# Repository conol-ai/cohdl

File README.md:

# CoHDL

CoHDL is the programming language that makes schematic (PCB) design AI-native — the way software became AI-native. AI generates and repairs hardware; the compiler is the oracle that grades it.

This is the **v2 ground-up implementation**, restarted 2026-07-13 from the redesigned language specification. The central thesis of the redesign: **strictness buys expressiveness** — push correctness into the type system wherever a mistake is structural (wrong units, unresolved pins, unsatisfied trait bounds), and reserve DRC only for genuinely emergent, whole-graph checks (net voltage, driver conflicts).

The previous implementation lives on the [`legacy`](https://github.com/conol-ai/cohdl/tree/legacy) branch. It is not being fixed; this is a fresh build informed by its lessons.

## Design repository

The source of truth for the language design is the Coherent Design Repository on conol.ai:
<https://conol.ai/share/note/tqrnb5h4l0dv8c14dkd17h4l>

A snapshot (taken 2026-07-13) is committed under [`docs/design/`](docs/design/). Key documents:

- [MVP Definition](docs/design/09-mvp-definition.md) — the scope line, demo scenario, and exit criteria this repository was built toward
- [Language Specification](docs/design/10-language-specification.md) — the compiled statement of what the language is (Accepted RFCs only)
- RFC-001…RFC-007 — the seven Accepted P0 RFCs: units-as-types, pin connection-obligation typing, trait satisfaction at impl time, DRC/type-system reclassification, collision-free designator allocation, nested fn call semantics, generics-over-specs
- RFC-008…RFC-018 — the post-MVP Accepted RFCs (compiler-implemented, with named open gaps recorded in [`docs/compliance-report.md`](docs/compliance-report.md) — notably RFC-016/017 on-disk dependency loading is not yet built, and RFC-014/015 real-client/partner acceptance passes remain open): structural variants, `cohdl fmt`, `cohdl check --json`, the formal error-code registry, `#[intent]` annotations, layout constraints, the LSP server (`cohdl lsp`, [`docs/lsp.md`](docs/lsp.md)), the IPC-2581 handoff document (`build --emit ipc2581`, [`docs/ipc2581.md`](docs/ipc2581.md)), the module system, the library registry, the pad/footprint format (`pad`/`footprint` geometry → `.kicad_mod` + IPC-2581 pins), and a real VS Code extension (`editors/vscode/`, packaging `cohdl lsp` with a TextMate grammar — RFC-019)

## MVP (v0.1) scope

The smallest slice of the spec that proves the thesis end-to-end:

1. **Parser** — traits, devices, free-standing `impl`, `fn` declarations/calls (nested), design bodies (`inst`, `net`, `nc`), the eleven unit-type literal forms
2. **Type checker** (the heart) — zero-coercion unit types, pin connection-obligation exhaustiveness, trait satisfaction with explicit mapping, generic resolution with trait-bound checking, nested fn expansion with cycle detection
3. **Residual DRC** — exactly four rules: voltage-exceed, polarity-mismatch, single-driver, multi-driver
4. **Designators** — collision-free allocator, `design.lock` with tombstones, `#[designator("…")]` overrides
5. **Codegen** — KiCad `.net` netlist + BOM CSV
6. **Minimal std library** — only the universal traits every component package needs
7. **Repair harness** — generate → check → repair loop driving an LLM against the compiler's diagnostics

The proof: an AI writes a board from a plain-language spec, the type checker catches its structural mistakes as precise compile errors, the AI repairs them from those diagnostics, and the result is a real, importable KiCad netlist with an honest BOM.

## Status

All MVP exit criteria are met, and all nineteen Accepted RFC areas (RFC-001…019) have implementation work with conformance suites. That is deliberately not a claim of full accepted-text compliance: requirements that are incomplete (e.g. RFC-014's real-editor acceptance pass and RFC-015's real-partner/Quilter import pass — both open), deliberately deviating (e.g. the E9xx code assignment, D003's role-aware reading, RFC-015's constraint mapping riding vendor extensions rather than native IPC semantics), or unrepresentable pending note-side amendments (e.g. RFC-013's E1005) are each recorded with rationale in the ledger, [`docs/compliance-report.md`](docs/compliance-report.md). Tested (`cargo test` — [`tests/exit_criteria.rs`](tests/exit_criteria.rs) maps 1:1 to the MVP checklist; each post-MVP RFC has its own conformance suite under `tests/`). The demo loop has run end-to-end: see [`docs/demo/`](docs/demo/) for transcripts (including a genuine E701 unresolved-required-pin catch + repair) and the emitted netlist/BOM. RFC/decision-record accuracy was audited claim-by-claim: [`docs/compliance-report.md`](docs/compliance-report.md). The KiCad checkpoint has been executed with real KiCad (pcbnew imported the netlist, resolved all footprints and pads; board + render in `docs/demo/`).

## Install

One line (macOS and Linux; installs to `~/.cohdl/bin`):

```sh
curl -fsSL https://raw.githubusercontent.com/conol-ai/cohdl/main/install.sh | sh
```

Prebuilt binaries (and their `sha256sums.txt`) are attached to every
[`vX.Y.Z` release](https://github.com/conol-ai/cohdl/releases); Windows users
download `cohdl-vX.Y.Z-x86_64-pc-windows-msvc.tar.gz` by hand. An installed
binary updates itself with `cohdl self-update` (`--check` reports without
installing). Building from source stays `cargo build` (toolchain pinned by
`rust-toolchain.toml`).

## Using it

```sh
cargo run -- check examples/sf32-miniboard       # SF32 miniboard: SiFli BLE eval board
cargo run -- build examples/rpi-pico2            # + designators, parts, KiCad .net + BOM CSV
cargo run -- check examples/rpi-pico2 --json     # structured diagnostics (RFC-010)
cargo run -- build examples/rpi-pico2 --emit ipc2581  # + IPC-2581 handoff document (RFC-015)
cargo run -- build examples/rpi-pico2 --emit kicad_pcb # + a native KiCad 10 board file — no KiCad needed
cargo run -- build examples/rpi-pico2 --emit easyeda   # + an EasyEDA / LCEDA Pro netlist (.enet)
cargo run -- build examples/rpi-pico2 --supplier acme   # + supplier BOM/map/CPL (RFC-034)
cargo run -- fmt lib --check                     # canonical-form gate (RFC-009)
cargo run -- lsp                                 # LSP server on stdio (RFC-014, docs/lsp.md)
cargo run -- search TPS59650                     # search registry packages + public parts
cargo run -- search TPS59650 --json              # the same bounded results as JSON
python3 harness/repair_loop.py                   # the generate → check → repair demo
```

Physical builds of placed designs also write `out/<name>-cpl.csv`, the
supplier-neutral five-column placement CSV. Under RFC-034,
repeatable `--supplier ID` selects each instance's own primary or eligible
alternate binding and writes `out/<name>-<ID>-bom.csv`,
`out/<name>-<ID>-map.json`, and (for physical builds)
`out/<name>-<ID>-cpl.csv`. The map preserves the selected entry identity and
placement transform; `tools/smt_pos.py --map` can apply it to the emitted
KiCad board. `--logical-only` remains a logical-artifact boundary: it emits
no neutral or supplier CPL, even when `--supplier` is present. Supplier BOM
and map remain available in that mode. Repeatable build option
`--bottom-rotation ID=VALUE` selects the bottom-side angle convention (`kicad`
or `mirrored`) for a supplier CPL; IDs must also be selected by `--supplier`
and default to `kicad`. Schema-2 maps record the convention actually used,
including in logical-only builds, and `tools/smt_pos.py --map` applies the same
rule (schema-1 maps retain `kicad` compatibility).

`cohdl search QUERY [--json]` is read-only discovery: it needs no project and
no registry login. Queries are trimmed, must contain at least three Unicode
scalar values, may be at most 128 UTF-8 bytes, and may not contain control
characters. Results identify the owning package and exact most-recently-
published version as well as importable public part paths and matching primary
or alternate manufacturer/MPN data; a valid query with no matches still exits
successfully. Use the standard option terminator when a literal query starts
with a hyphen, for example `cohdl search -- -12V`. “Most recently published”
is publication chronology, not the greatest semantic version chosen by an
unversioned `cohdl add`/`cohdl update`.
The package and part result families are bounded independently; each exposes
`has_more` when truncated and never a total count. Human output separates the
two families, while `--json` returns the same rows as one discovery document.
For rollout, owners of existing packages backfill the current searchable
version once with `cohdl docs --publish`; this does not change its tar or hash.

`std` is a core-traits-only prelude; it carries no devices, parts, pads, or
footprints. Shipped component packages include `passive`, `connectors`, `usb`,
`esd`, `diode`, `flash`, `ldo`, `led`, `mic`, `mosfet`, `osc`, and
manufacturer packages for Espressif, Raspberry Pi, Richtek, ST, and TI.
Projects pin every package they use to an exact version under
`[dependencies]`; see [`lib/README.md`](lib/README.md) for the complete
namespace map.

Two reference designs live in `examples/`: Raspberry Pi **Pico 2** and the
**SF32 miniboard**. (The **OpenMicro** macropad — the wired STM32F072 v1 and
its wireless SF32LB52 successor v2 — graduated to its own repository,
`openmicrokbd`, which carries the whole product: hardware source, firmware,
host app, and fab releases under `hw/v1/` and `hw/v2/`.)

An **AI voice robot-dog mainboard** is in progress and not yet in the tree; its
exit-criteria test is checked in but ignored until the example lands. It
combines an ESP32-S3-N8R2, stereo I2S microphones,
isolated speaker playback, a translated 1.8 V IMU domain, USB-C, a protected
default-off 7 A actuator rail, and eight 5 V servo PWM channels. Keyed 4/6-pin
Micro-Fit harnesses prevent the BEC input from being interchanged with a leg.

### Build artifacts

`cohdl build` writes to `out/` (or `--out-dir`): the KiCad netlist (`<name>.net`), the BOM (`<name>-bom.csv`), the designator lock (`design.lock` in the project root), a `.kicad_mod` per pad-bearing footprint under `out/footprints/` (RFC-018), and — only when the design declares layout metadata — the layout-constraint artifact `<name>-layout.json` (schema: [`docs/layout-json.md`](docs/layout-json.md)). With `--emit ipc2581` it additionally writes the IPC-2581B1 handoff document `<name>.xml` (RFC-015; [`docs/ipc2581.md`](docs/ipc2581.md)), with `--emit kicad_pcb` a native KiCad 10 board file `<name>.kicad_pcb` — placements, net-bound footprints, and the board outline, with no KiCad installation involved ([`docs/kicad_pcb.md`](docs/kicad_pcb.md)), and with `--emit easyeda` an EasyEDA / LCEDA Pro netlist `<name>.enet` for **File → Import → Netlist** ([`docs/easyeda.md`](docs/easyeda.md)); the flags compose. Stale layout/IPC/board artifacts are removed when their source data is gone (the IPC document only if CoHDL wrote it — its completeness marker establishes ownership).

### Looking at a design

A checked design can be read back as an interactive schematic-style board —
every instance, net and pin the compiler resolved, searchable and traceable,
with datasheets and to-scale footprint previews in a side panel. It is a
read-only projection: the `.cohdl` source stays the only thing that defines
the circuit.

On macOS, download the signed, notarized app from the latest
[`explorer-v*` release](https://github.com/conol-ai/cohdl/releases?q=explorer&expanded=true)
(mount the DMG, drag to Applications, pick a project). Or run it from source:

```sh
cd explorer/web && npm install && npm run build   # once
cd ../extractor
COHDL_LIB=../../lib cargo run --release -- ../../examples/rpi-pico2 \
    --serve --dist ../web/dist --port 5199        # http://127.0.0.1:5199/
```

Editing any source file re-extracts and refreshes the page within ~500 ms; a
source that fails to compile keeps the last good view and shows the
diagnostics. Extraction, layout and wire routing are deterministic code — the
same source always draws the same board. An agent's only input is the
partition file `explorer/views/<Design>.view.json`, which names the page tabs
and the region each part belongs to; the contract for writing one is
[`explorer/skills/view-gen/SKILL.md`](explorer/skills/view-gen/SKILL.md).
See [`explorer/README.md`](explorer/README.md).

### Exit codes

`0` = clean (warnings and a valid no-match search are allowed); `1` = the
accepted command failed (source errors, non-canonical `fmt --check`, or an E1204
search registry/protocol failure); `2` = invocation-level failure (bad flags,
an invalid search query, missing project, design selection, nothing to build);
`3` = `cohdl suppliers` found an `unknown` or `mismatched` audited binding
(out-of-stock, unbound, and unlisted suppliers do not change the exit code).
Human diagnostics use stderr. A successful `search --json` emits its discovery
document on stdout, and an E1204 failure in that mode emits the existing
diagnostic JSON there; bad invocations remain prose-only on stderr. See the
formal [`docs/error-codes.md`](docs/error-codes.md) registry. Note: RFC-010's
text reserves stderr prose for pre-collection failures, so classifying
post-collection selection failures this way is a documented deviation pending
a note-side amendment (or a v2 schema envelope).

## License

MIT — see [`LICENSE`](LICENSE). This covers the compiler crate, the libraries
under `lib/`, the reference designs in `examples/`, the registry
server in `registry/`, the VS Code extension in `editors/vscode/`, and the
tooling in `tools/` and `harness/`.

Third-party material is not covered by that grant: the manufacturer documents
under `lib/*/docs/` keep their owners' terms, KiCad-derived footprints are
CC-BY-SA-4.0 as each such package records in its manifest and license files, and the supplier
catalog facts and assembly-preview captures under `tools/sourcing_data/` are
described in [`tools/sourcing_data/NOTICE.md`](tools/sourcing_data/NOTICE.md).

Every package published to registry.cohdl.org must declare its own
`[package] license`; every package shipped under `lib/` declares `MIT`.

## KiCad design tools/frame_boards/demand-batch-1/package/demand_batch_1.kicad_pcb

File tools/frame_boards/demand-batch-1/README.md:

# Demand batch 1 preview board

**Built, not previewed, not evidence.** This directory holds the input
manifest for an assembler preview of ten part numbers whose library parts
are unbound. Nothing here is a binding, and no frame row is written from
it.

## Why it exists

The parts added on 2026-11-25 (`load-switch` 0.2.2, `diode` 0.1.3,
`transistor` 0.2.2) have candidate LCSC part numbers but no
`supplier lcsc` clause: a binding needs a frame row with evidence in
`tools/sourcing_data/jlc_frames.json`, and that evidence is an assembler
preview read by a person. This board is the input for that preview.

## Rows

Each row declares a local part with the candidate part number on the
library device and land, with a zero mapping, placed four times: top 0 and
37 degrees, bottom 0 and 37 degrees, in 14 mm boxes on a 16 mm pitch (the
preview board 5 layout).

| Library part (unbound) | Candidate | Land |
|---|---|---|
| `load_switch::LOADSW_TPS2553DBVR` | C55266 | `load_switch::FP_TI_DBV0006A` |
| `load_switch::LOADSW_TPS2553DBVR_1` | C111738 | `load_switch::FP_TI_DBV0006A` |
| `load_switch::LOADSW_TPS2552DBVR` | C46506 | `load_switch::FP_TI_DBV0006A` |
| `diode::TVS_VISHAY_SMBJ30A` | C1973126 | `do214::DIOM5336X265N` |
| `diode::TVS_MDD_SMBJ30A` | C113998 | `do214::DIOM5336X265N` |
| `diode::TVS_HONGJIACHENG_SMBJ30A` | C19077584 | `do214::DIOM5336X265N` |
| `diode::TVS_VISHAY_SMBJ30CA` | C553967 | `do214::DIOM5336X265N` |
| `diode::TVS_MDD_SMBJ30CA` | C113999 | `do214::DIOM5336X265N` |
| `diode::TVS_HONGJIACHENG_SMBJ30CA` | C19077585 | `do214::DIOM5336X265N` |
| `transistor::FET_BSS138` | C52895 | `sot::SOT3P190X290X130N` |

The manufacturer, MPN, package, class and stock in each row are what the
part's JLCPCB page read on 2026-11-25. None of the ten is in
`tools/sourcing_data/lcsc_map.json`.

## State on 2026-11-25

- `manifest.json` was written by hand in the input format of
  `tools/jlc_frame_board.py`; there is no generator script for it.
- **The board package is built** (library at commit `537c43d`, Python
  3.11.0rc1, `kicad-cli` 10.0.8):

  ```sh
  python3.11 -I tools/jlc_frame_board.py tools/frame_boards/demand-batch-1/manifest.json \
    -o BOARD --cohdl target/debug/cohdl
  ```

  It reported `generated 40 placements`. A 180 x 75 mm board.
- `package/` is a copy of that output: `fabrication/` (Gerbers, drill file
  and `SHA256SUMS`), `demand_batch_1.kicad_pcb`,
  `demand_batch_1-lcsc-bom.csv`, `demand_batch_1-lcsc-cpl.csv`,
  `demand_batch_1-cpl.csv` and the tool's `CHECKLIST.md`.
- `render/` holds `kicad-cli pcb render` images of that board file:
  `top.png` and `bottom.png` (each side seen from its own side), and one
  480 px crop per copy, named `<C-number>_<designator>_<side>_<angle>.png`
  (16 mm square about the placement). The renders show our copper and
  silkscreen only. They contain no supplier model and are not a preview.
- **Checked against the board file, not against any preview:** all ten part
  numbers are in the LCSC BOM with four designators each; every part
  number has a top 0, top 37, bottom 0 and bottom 37 copy at its manifest
  position; each copy is on the intended land with the intended pad
  numbers and sizes (six 1.1 x 0.6 mm pads on `FP_TI_DBV0006A`, two
  2.10 x 2.26 mm on `DIOM5336X265N`, three 0.8 x 0.9 mm on
  `SOT3P190X290X130N`).
- **The silkscreen carries reference designators.** Preview board 5 left
  them out of the Gerber silkscreen because text beside a part disturbed
  the measuring script's readings. Regenerate without them if the readings
  are to be measured by `measure_preview.py`.
- Nothing was uploaded. No preview was run, no reading exists, and no row
  of `tools/sourcing_data/jlc_frames.json` or `lcsc_map.json` was written.

## What a person still has to confirm

For each part number, on JLCPCB's assembly preview of the built board:

1. The model is drawn, on our pads, on all four copies.
2. Pin 1 (SOT-23-6, SOT-23) or the cathode band (unidirectional SMBJ) sits
   at our pad 1; if it reads a quarter or half turn, that reading is a
   candidate rotation, to be confirmed on a second board with the
   candidate applied, as preview board 5 did.
3. For the bidirectional SMBJ parts, the body's long axis lies along the
   pad axis and is centred (the body-only rule of
   `docs/library-supplier-plan.md`); orientation is known mod 180 only.

Only after that review does a part get a frame row with `evidence`, a map
row from a promoted `tools/lcsc_backfill.py` run, and its
`supplier lcsc` clause in a new package version.

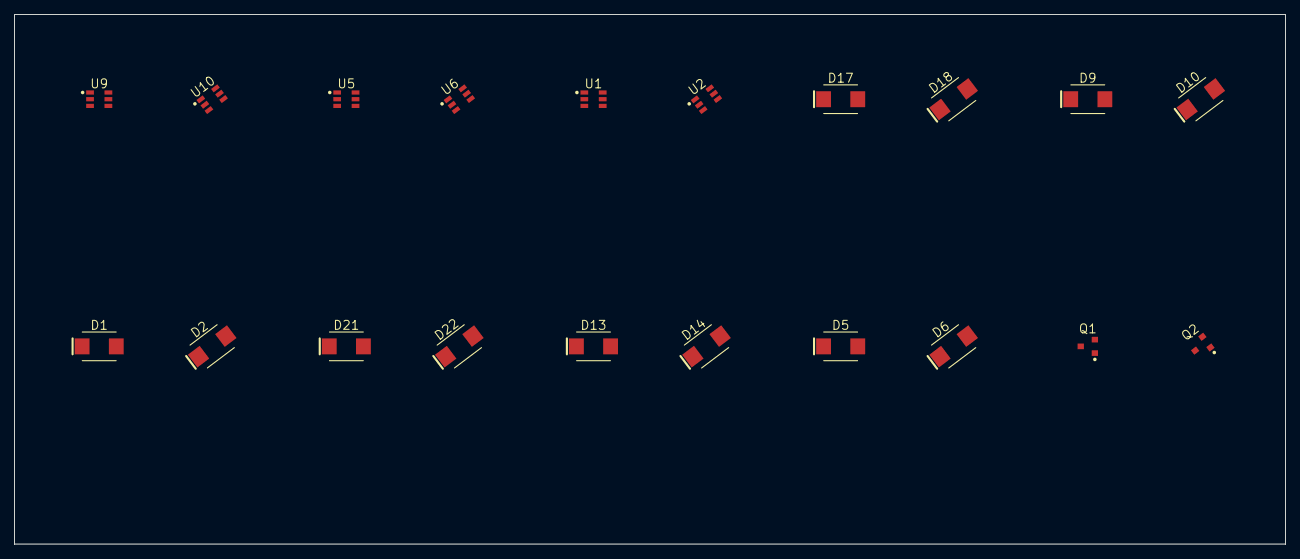
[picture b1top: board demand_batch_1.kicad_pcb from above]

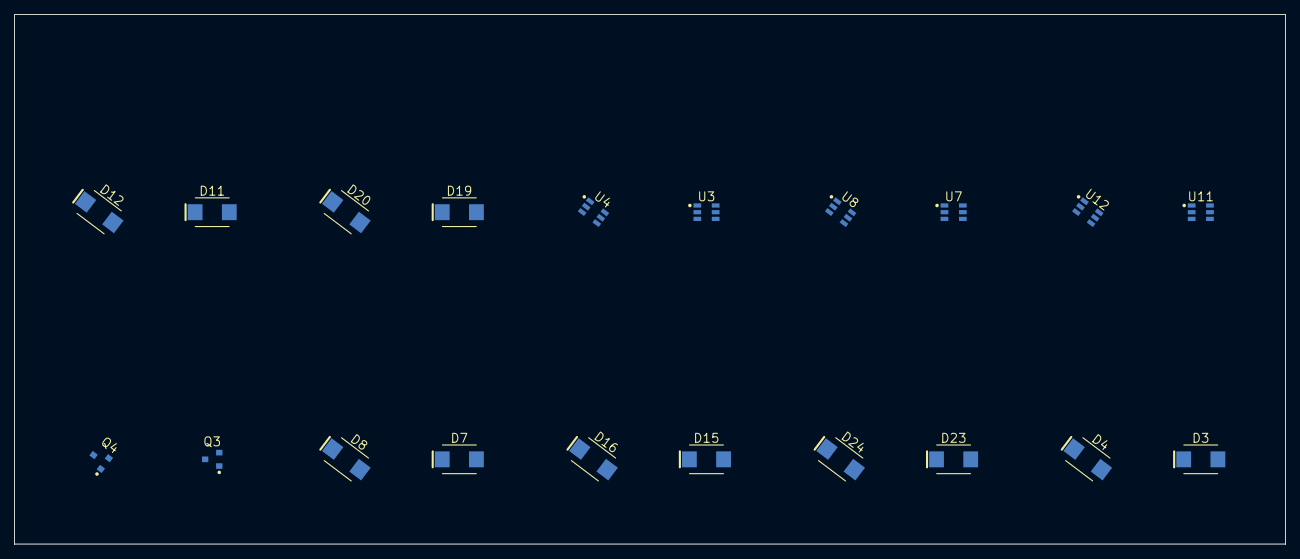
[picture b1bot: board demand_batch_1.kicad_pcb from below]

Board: 2 copper layers, 180.0 x 75.0 mm, 40 parts (20 on the bottom side), 2 nets, no tracks yet.

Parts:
D1, D2, D3, D4, D9, D10, D11, D12, D17, D18, D19, D20: TVS_SMBJ_Uni; do214-DIOM5336X265N
D5, D6, D7, D8, D13, D14, D15, D16, D21, D22, D23, D24: TVS_SMBJ_Bi; do214-DIOM5336X265N
Q1, Q2, Q3, Q4: BSS138; sot-SOT3P190X290X130N
U1, U2, U3, U4: TPS2552; load_switch-FP_TI_DBV0006A
U5, U6, U7, U8, U9, U10, U11, U12: TPS2553; load_switch-FP_TI_DBV0006A

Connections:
N0: D1.1, D2.1, D3.1, D4.1, D5.1, D6.1, D7.1, D8.1, D9.1, D10.1, D11.1, D12.1, D13.1, D14.1, D15.1, D16.1, D17.1, D18.1, D19.1, D20.1, D21.1, D22.1, D23.1, D24.1, Q1.1, Q2.1, Q3.1, Q4.1, U1.1, U2.1, U3.1, U4.1, U5.1, U6.1, U7.1, U8.1, U9.1, U10.1, U11.1, U12.1
N1: D1.2, D2.2, D3.2, D4.2, D5.2, D6.2, D7.2, D8.2, D9.2, D10.2, D11.2, D12.2, D13.2, D14.2, D15.2, D16.2, D17.2, D18.2, D19.2, D20.2, D21.2, D22.2, D23.2, D24.2, Q1.2, Q2.2, Q3.2, Q4.2, U1.2, U2.2, U3.2, U4.2, U5.2, U6.2, U7.2, U8.2, U9.2, U10.2, U11.2, U12.2

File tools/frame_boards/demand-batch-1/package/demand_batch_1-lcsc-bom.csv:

Comment,Designator,Footprint,LCSC Part #
"TPS2553DBVR-1","U5,U6,U7,U8","FP_TI_DBV0006A","C111738"
"SMBJ30A","D9,D10,D11,D12","DIOM5336X265N","C113998"
"SMBJ30CA","D13,D14,D15,D16","DIOM5336X265N","C113999"
"SMBJ30A","D1,D2,D3,D4","DIOM5336X265N","C19077584"
"SMBJ30CA","D5,D6,D7,D8","DIOM5336X265N","C19077585"
"SMBJ30A-E3/52","D17,D18,D19,D20","DIOM5336X265N","C1973126"
"TPS2552DBVR","U1,U2,U3,U4","FP_TI_DBV0006A","C46506"
"BSS138","Q1,Q2,Q3,Q4","SOT3P190X290X130N","C52895"
"TPS2553DBVR","U9,U10,U11,U12","FP_TI_DBV0006A","C55266"
"SMBJ30CA-E3/52","D21,D22,D23,D24","DIOM5336X265N","C553967"

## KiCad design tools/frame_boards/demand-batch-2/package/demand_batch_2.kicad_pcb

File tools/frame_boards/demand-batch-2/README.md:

# Demand batch 2 preview board

**Built, not previewed, not evidence.** This directory holds the input
manifest, the built board package and renders for an assembler preview of
23 candidate part numbers whose library parts are unbound. Nothing here is
a binding, and no frame row is written from it.

## Why it exists

The parts added on 2026-11-25 (`son` 0.1.0, `load-switch` 0.2.2, `ldo`
0.1.3, `dcdc` 0.1.2, `@ti/power-switch` 0.1.1, `fuse` 0.1.0) have
candidate LCSC part numbers but no `supplier lcsc` clause: a binding needs
a frame row with evidence in `tools/sourcing_data/jlc_frames.json`, and
that evidence is an assembler preview read by a person. This board is the
input for that preview.

## Rows

Each row declares a local part with the candidate part number on the
library device and land, with a zero mapping, placed four times: top 0 and
37 degrees, bottom 0 and 37 degrees, in 14 mm boxes on a 16 mm pitch.

| Library part (unbound) | Candidate | Land |
|---|---|---|
| `load_switch::LOADSW_TPS2553DRVR` | C138719 | `son::TI_DRV0006A` |
| `load_switch::LOADSW_TPS2553DRVR_1` | C411878 | `son::TI_DRV0006A` |
| `load_switch::LOADSW_TPS2552DRVR` | C473916 | `son::TI_DRV0006A` |
| `ldo::LDO_LP5912_3V3` | C524780 | `son::TI_DRV0006A` |
| `ldo::LDO_LP5912_1V8` | C2876234 | `son::TI_DRV0006A` |
| `ldo::LDO_LP5912_5V0` | C2761351 | `son::TI_DRV0006A` |
| `ldo::LDO_TLV75533PDRVR` | C2861750 | `son::TI_DRV0006A` |
| `ldo::LDO_TLV75512PDRVR` | C2866903 | `son::TI_DRV0006A` |
| `ldo::LDO_TLV75525PDRVR` | C544744 | `son::TI_DRV0006A` |
| `dcdc::DCDC_LMR36520ADDAR` | C2879422 | `dcdc::TI_DDA0008B` |
| `dcdc::DCDC_LMR36520FADDAR` | C1858395 | `dcdc::TI_DDA0008B` |
| `ti_power_switch::EFUSE_TPS26630RGER` | C1850276 | `ti_power_switch::TI_RGE0024H` |
| `ti_power_switch::EFUSE_TPS26631RGER` | C1850273 | `ti_power_switch::TI_RGE0024H` |
| `ti_power_switch::EFUSE_TPS26632RGER` | C1850278 | `ti_power_switch::TI_RGE0024H` |
| `ti_power_switch::EFUSE_TPS26620DRCR` | C1848361 | `ti_power_switch::TI_DRC0010J` |
| `ti_power_switch::EFUSE_TPS26621DRCR` | C1848341 | `ti_power_switch::TI_DRC0010J` |
| `ti_power_switch::EFUSE_TPS259827ONRGET` | C2155765 | `ti_power_switch::TI_RGE0024M` |
| `ti_power_switch::EFUSE_TPS259827ONRGER` | C2155761 | `ti_power_switch::TI_RGE0024M` |
| `fuse::FUSE_451_0A5` | C142836 | `fuse::FP_LITTELFUSE_NANO2` |
| `fuse::FUSE_451_1A` | C3099 | `fuse::FP_LITTELFUSE_NANO2` |
| `fuse::FUSE_451_2A` | C99547 | `fuse::FP_LITTELFUSE_NANO2` |
| `fuse::FUSE_451_3A` | C13982 | `fuse::FP_LITTELFUSE_NANO2` |
| `fuse::FUSE_451_4A` | C27515 | `fuse::FP_LITTELFUSE_NANO2` |

The manufacturer and MPN in each row are the library part's. The `stock`
field is the local jlcparts snapshot of 2026-11-25; the part pages were
not read (C3099 excepted), so no row carries a page date, package or
class. None of the 23 is in `tools/sourcing_data/lcsc_map.json`. Several
are too thinly stocked to place 20 pieces: C1850276 has 48, C1848361 has
196.

In each row the first two pins (a supply input and a ground, or the two
fuse terminals) form the board's two nets; the tool marks the remaining
listed pins unconnected.

## State on 2026-11-25

- `manifest.json` was written by hand in the input format of
  `tools/jlc_frame_board.py`; there is no generator script for it.
- **The board package is built** (Python 3.11.0rc1, `kicad-cli` 10.0.8):

  ```sh
  python3.11 -I tools/jlc_frame_board.py tools/frame_boards/demand-batch-2/manifest.json \
    -o BOARD --cohdl target/debug/cohdl
  ```

  It reported `generated 92 placements`. A 215 x 145 mm board.
- **Rebuilt from the library at commit `b75dc9b`.** The first build
  predated two land corrections in `@ti/power-switch`: the `TI_DRC0010J`
  finger paste apertures (now centred 1.53 mm from the centre line, commit
  `99799f9`) and the `TI_RGE0024M` pad-25 via rows (now at -0.15 mm and
  -1.10 mm, commit `b75dc9b`). `package/` and `render/` were replaced
  whole by the rebuild, so the paste Gerbers, drill file and board file
  here match the library. Placements and every other land are the same as
  in the first build. An archive made from the first build is stale.
- `package/` is a copy of that output: `fabrication/` (Gerbers, drill file
  and `SHA256SUMS`), `demand_batch_2.kicad_pcb`,
  `demand_batch_2-lcsc-bom.csv`, `demand_batch_2-lcsc-cpl.csv`,
  `demand_batch_2-cpl.csv` and the tool's `CHECKLIST.md`.
- `render/` holds 94 `kicad-cli pcb render` images of that board file:
  `top.png` and `bottom.png` (each side seen from its own side), and one
  480 px crop per copy, 92 in all, named
  `<C-number>_<designator>_<side>_<angle>.png` (16 mm square about the
  placement). The renders show our copper, paste and silkscreen only.
  They contain no supplier model and are not a preview.
- **Checked against the board file, not against any preview:** all 23
  part numbers are in the LCSC BOM with four designators each; every part
  number has a top 0, top 37, bottom 0 and bottom 37 copy at its manifest
  position; each copy is on the intended land with the intended number of
  distinct pad numbers (7 on `TI_DRV0006A`, 9 on `TI_DDA0008B`, 25 on
  `TI_RGE0024H`, 26 on `TI_RGE0024M`, 11 on `TI_DRC0010J`, 2 on
  `FP_LITTELFUSE_NANO2`).
- **The silkscreen carries reference designators.** Preview board 5 left
  them out of the Gerber silkscreen because text beside a part disturbed
  the measuring script's readings. Regenerate without them if the readings
  are to be measured by `measure_preview.py`.
- Nothing was uploaded. No preview was run, no reading exists, and no row
  of `tools/sourcing_data/jlc_frames.json` or `lcsc_map.json` was written.

## What a person still has to confirm

For each part number, on JLCPCB's assembly preview of the built board:

1. The model is drawn, on our pads, on all four copies, and it is the
   package the land is for (a 2 x 2 mm WSON-6, an 8-pin PowerPAD SOIC, a
   4 x 4 mm VQFN-24, a 3 x 3 mm VSON-10, a 2410 fuse).
2. For the ICs, the model's pin 1 mark sits at our pad 1 (the silkscreen
   dot). A quarter or half turn is a candidate rotation, to be confirmed
   on a second board with the candidate applied, as preview board 5 did.
3. For the fuses, which have no pin 1 and no polarity, the body's long
   axis lies along the pad axis and is centred; orientation is known mod
   180 only.
4. For the three WSON-6 families sharing `son::TI_DRV0006A`, each part
   number is read on its own: a rotation found for one says nothing about
   another.

Only after that review does a part get a frame row with `evidence`, a map
row from a promoted `tools/lcsc_backfill.py` run, and its
`supplier lcsc` clause in a new package version.

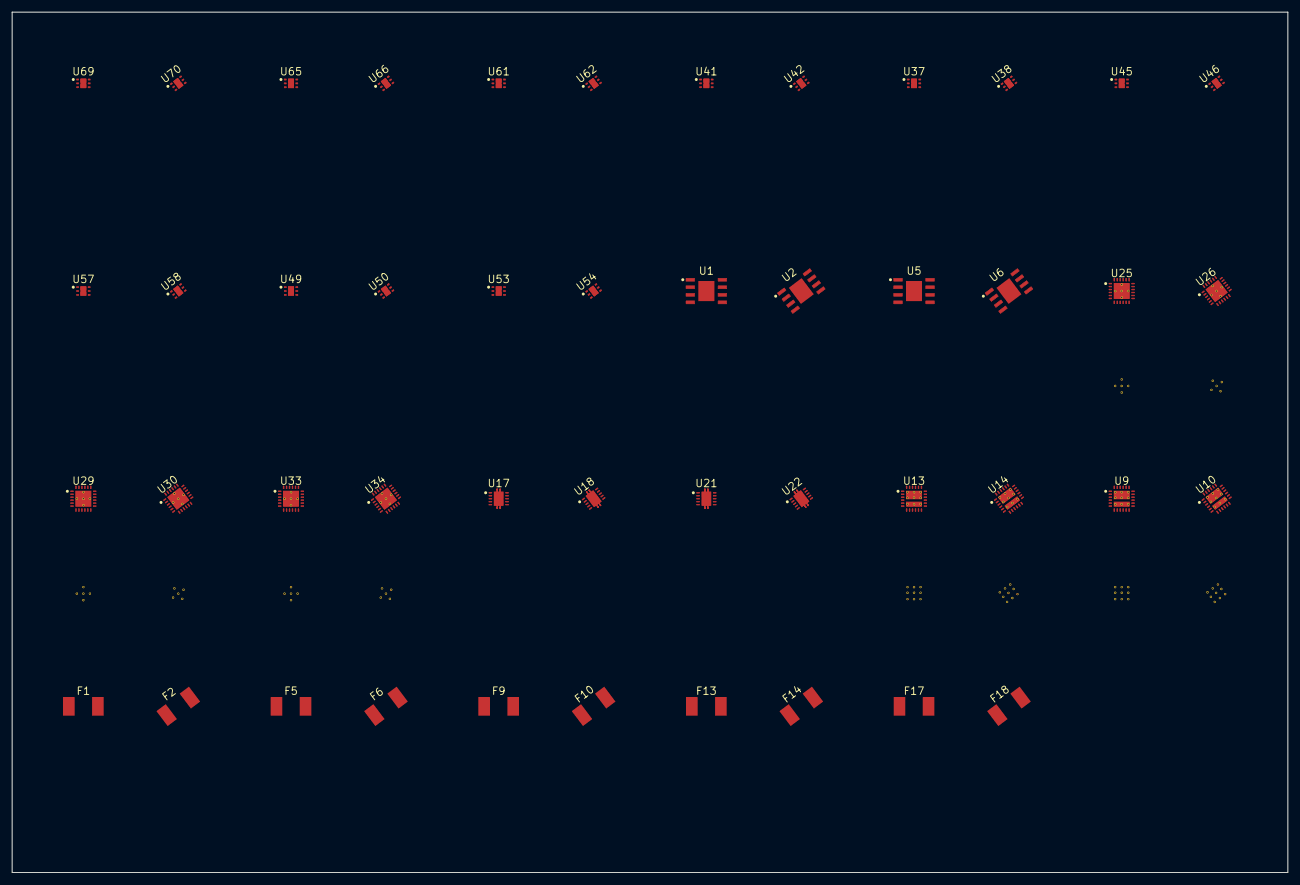
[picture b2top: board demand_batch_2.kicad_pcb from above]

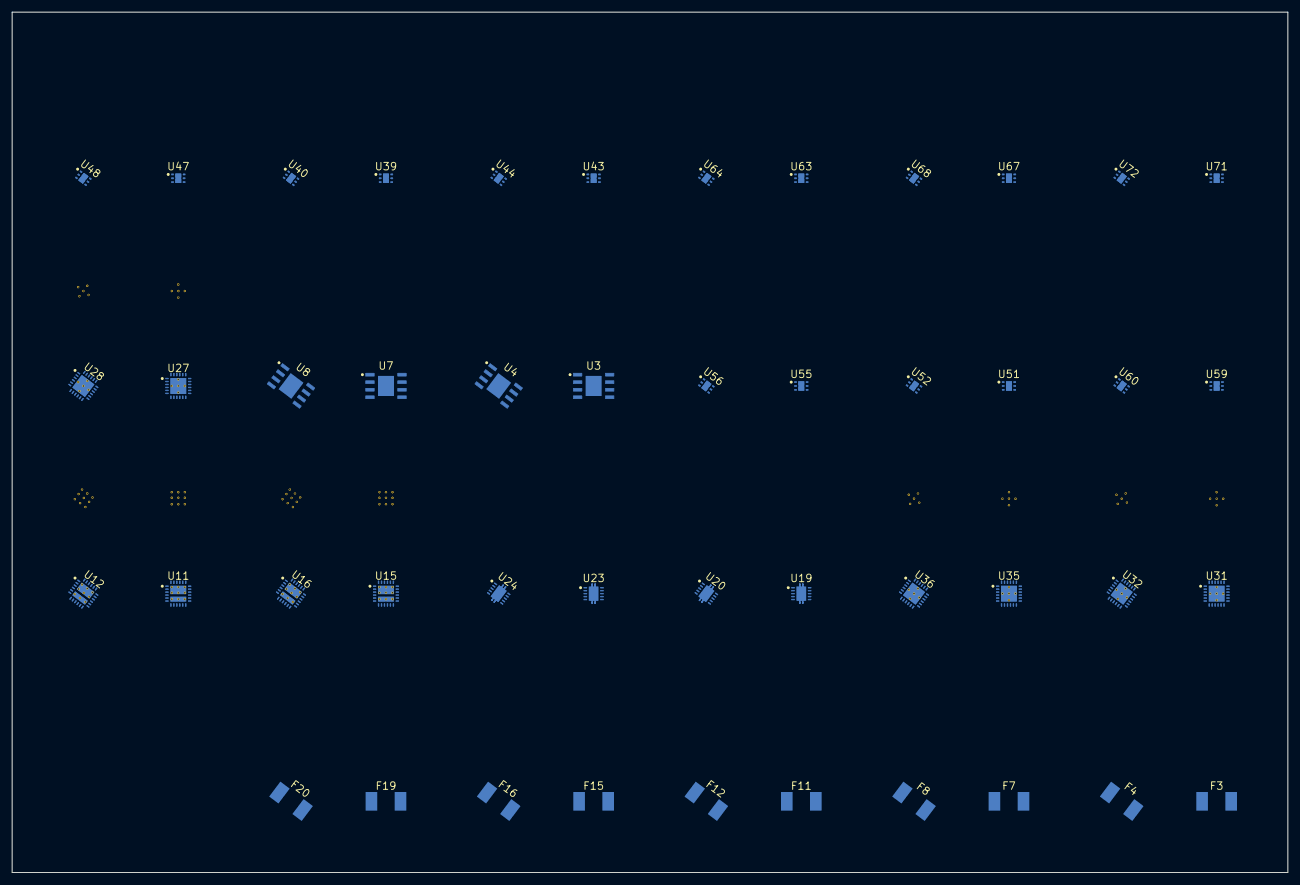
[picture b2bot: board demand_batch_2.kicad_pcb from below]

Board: 2 copper layers, 215.0 x 145.0 mm, 92 parts (46 on the bottom side), 2 nets, no tracks yet.

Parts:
F1, F2, F3, F4: Fuse_451_0A5; fuse-FP_LITTELFUSE_NANO2
F5, F6, F7, F8: Fuse_451_1A; fuse-FP_LITTELFUSE_NANO2
F9, F10, F11, F12: Fuse_451_2A; fuse-FP_LITTELFUSE_NANO2
F13, F14, F15, F16: Fuse_451_3A; fuse-FP_LITTELFUSE_NANO2
F17, F18, F19, F20: Fuse_451_4A; fuse-FP_LITTELFUSE_NANO2
U1, U2, U3, U4, U5, U6, U7, U8: LMR36520; dcdc-TI_DDA0008B
U9, U10, U11, U12, U13, U14, U15, U16: TPS259827O; ti_power_switch-TI_RGE0024M
U17, U18, U19, U20, U21, U22, U23, U24: TPS26620; ti_power_switch-TI_DRC0010J
U25, U26, U27, U28: TPS26630; ti_power_switch-TI_RGE0024H
U29, U30, U31, U32: TPS26631; ti_power_switch-TI_RGE0024H
U33, U34, U35, U36: TPS26632; ti_power_switch-TI_RGE0024H
U37, U38, U39, U40: LP5912_1V8; son-TI_DRV0006A
U41, U42, U43, U44: LP5912_3V3; son-TI_DRV0006A
U45, U46, U47, U48: LP5912_5V0; son-TI_DRV0006A
U49, U50, U51, U52: TLV75512P_DRV; son-TI_DRV0006A
U53, U54, U55, U56: TLV75525P_DRV; son-TI_DRV0006A
U57, U58, U59, U60: TLV75533P_DRV; son-TI_DRV0006A
U61, U62, U63, U64: TPS2552_DRV; son-TI_DRV0006A
U65, U66, U67, U68, U69, U70, U71, U72: TPS2553_DRV; son-TI_DRV0006A

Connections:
N0: F1.1, F2.1, F3.1, F4.1, F5.1, F6.1, F7.1, F8.1, F9.1, F10.1, F11.1, F12.1, F13.1, F14.1, F15.1, F16.1, F17.1, F18.1, F19.1, F20.1, U1.2, U2.2, U3.2, U4.2, U5.2, U6.2, U7.2, U8.2, U9.1, U9.2, U9.3, U9.16, U9.25, U10.1, U10.2, U10.3, U10.16, U10.25, U11.1, U11.2, U11.3, U11.16, U11.25, U12.1, U12.2, U12.3, U12.16, U12.25, U13.1, U13.2, U13.3, U13.16, U13.25, U14.1, U14.2, U14.3, U14.16, U14.25, U15.1, U15.2, U15.3, U15.16, U15.25, U16.1, U16.2, U16.3, U16.16, U16.25, U17.1, U18.1, U19.1, U20.1, U21.1, U22.1, U23.1, U24.1, U25.1, U25.2, U26.1, U26.2, U27.1, U27.2, U28.1, U28.2, U29.1, U29.2, U30.1, U30.2, U31.1, U31.2, U32.1, U32.2, U33.1, U33.2, U34.1, U34.2, U35.1, U35.2, U36.1, U36.2, U37.6, U38.6, U39.6, U40.6, U41.6, U42.6, U43.6, U44.6, U45.6, U46.6, U47.6, U48.6, U49.6, U50.6, U51.6, U52.6, U53.6, U54.6, U55.6, U56.6, U57.6, U58.6, U59.6, U60.6, U61.6, U62.6, U63.6, U64.6, U65.6, U66.6, U67.6, U68.6, U69.6, U70.6, U71.6, U72.6
N1: F1.2, F2.2, F3.2, F4.2, F5.2, F6.2, F7.2, F8.2, F9.2, F10.2, F11.2, F12.2, F13.2, F14.2, F15.2, F16.2, F17.2, F18.2, F19.2, F20.2, U1.1, U2.1, U3.1, U4.1, U5.1, U6.1, U7.1, U8.1, U9.4, U9.5, U9.14, U9.26, U10.4, U10.5, U10.14, U10.26, U11.4, U11.5, U11.14, U11.26, U12.4, U12.5, U12.14, U12.26, U13.4, U13.5, U13.14, U13.26, U14.4, U14.5, U14.14, U14.26, U15.4, U15.5, U15.14, U15.26, U16.4, U16.5, U16.14, U16.26, U17.6, U18.6, U19.6, U20.6, U21.6, U22.6, U23.6, U24.6, U25.8, U25.25, U26.8, U26.25, U27.8, U27.25, U28.8, U28.25, U29.8, U29.25, U30.8, U30.25, U31.8, U31.25, U32.8, U32.25, U33.8, U33.25, U34.8, U34.25, U35.8, U35.25, U36.8, U36.25, U37.5, U38.5, U39.5, U40.5, U41.5, U42.5, U43.5, U44.5, U45.5, U46.5, U47.5, U48.5, U49.3, U49.7, U50.3, U50.7, U51.3, U51.7, U52.3, U52.7, U53.3, U53.7, U54.3, U54.7, U55.3, U55.7, U56.3, U56.7, U57.3, U57.7, U58.3, U58.7, U59.3, U59.7, U60.3, U60.7, U61.5, U61.7, U62.5, U62.7, U63.5, U63.7, U64.5, U64.7, U65.5, U65.7, U66.5, U66.7, U67.5, U67.7, U68.5, U68.7, U69.5, U69.7, U70.5, U70.7, U71.5, U71.7, U72.5, U72.7

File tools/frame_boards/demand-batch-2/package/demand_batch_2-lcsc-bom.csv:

Comment,Designator,Footprint,LCSC Part #
"TPS2553DRVR","U69,U70,U71,U72","TI_DRV0006A","C138719"
"0451003.MRL","F13,F14,F15,F16","FP_LITTELFUSE_NANO2","C13982"
"0451.500MRL","F1,F2,F3,F4","FP_LITTELFUSE_NANO2","C142836"
"TPS26621DRCR","U21,U22,U23,U24","TI_DRC0010J","C1848341"
"TPS26620DRCR","U17,U18,U19,U20","TI_DRC0010J","C1848361"
"TPS26631RGER","U29,U30,U31,U32","TI_RGE0024H","C1850273"
"TPS26630RGER","U25,U26,U27,U28","TI_RGE0024H","C1850276"
"TPS26632RGER","U33,U34,U35,U36","TI_RGE0024H","C1850278"
"LMR36520FADDAR","U5,U6,U7,U8","TI_DDA0008B","C1858395"
"TPS259827ONRGER","U9,U10,U11,U12","TI_RGE0024M","C2155761"
"TPS259827ONRGET","U13,U14,U15,U16","TI_RGE0024M","C2155765"
"0451004.MRL","F17,F18,F19,F20","FP_LITTELFUSE_NANO2","C27515"
"LP5912-5.0DRVR","U45,U46,U47,U48","TI_DRV0006A","C2761351"
"TLV75533PDRVR","U57,U58,U59,U60","TI_DRV0006A","C2861750"
"TLV75512PDRVR","U49,U50,U51,U52","TI_DRV0006A","C2866903"
"LP5912-1.8DRVR","U37,U38,U39,U40","TI_DRV0006A","C2876234"
"LMR36520ADDAR","U1,U2,U3,U4","TI_DDA0008B","C2879422"
"0451001.MRL","F5,F6,F7,F8","FP_LITTELFUSE_NANO2","C3099"
"TPS2553DRVR-1","U65,U66,U67,U68","TI_DRV0006A","C411878"
"TPS2552DRVR","U61,U62,U63,U64","TI_DRV0006A","C473916"
"LP5912-3.3DRVR","U41,U42,U43,U44","TI_DRV0006A","C524780"
"TLV75525PDRVR","U53,U54,U55,U56","TI_DRV0006A","C544744"
"0451002.MRL","F9,F10,F11,F12","FP_LITTELFUSE_NANO2","C99547"

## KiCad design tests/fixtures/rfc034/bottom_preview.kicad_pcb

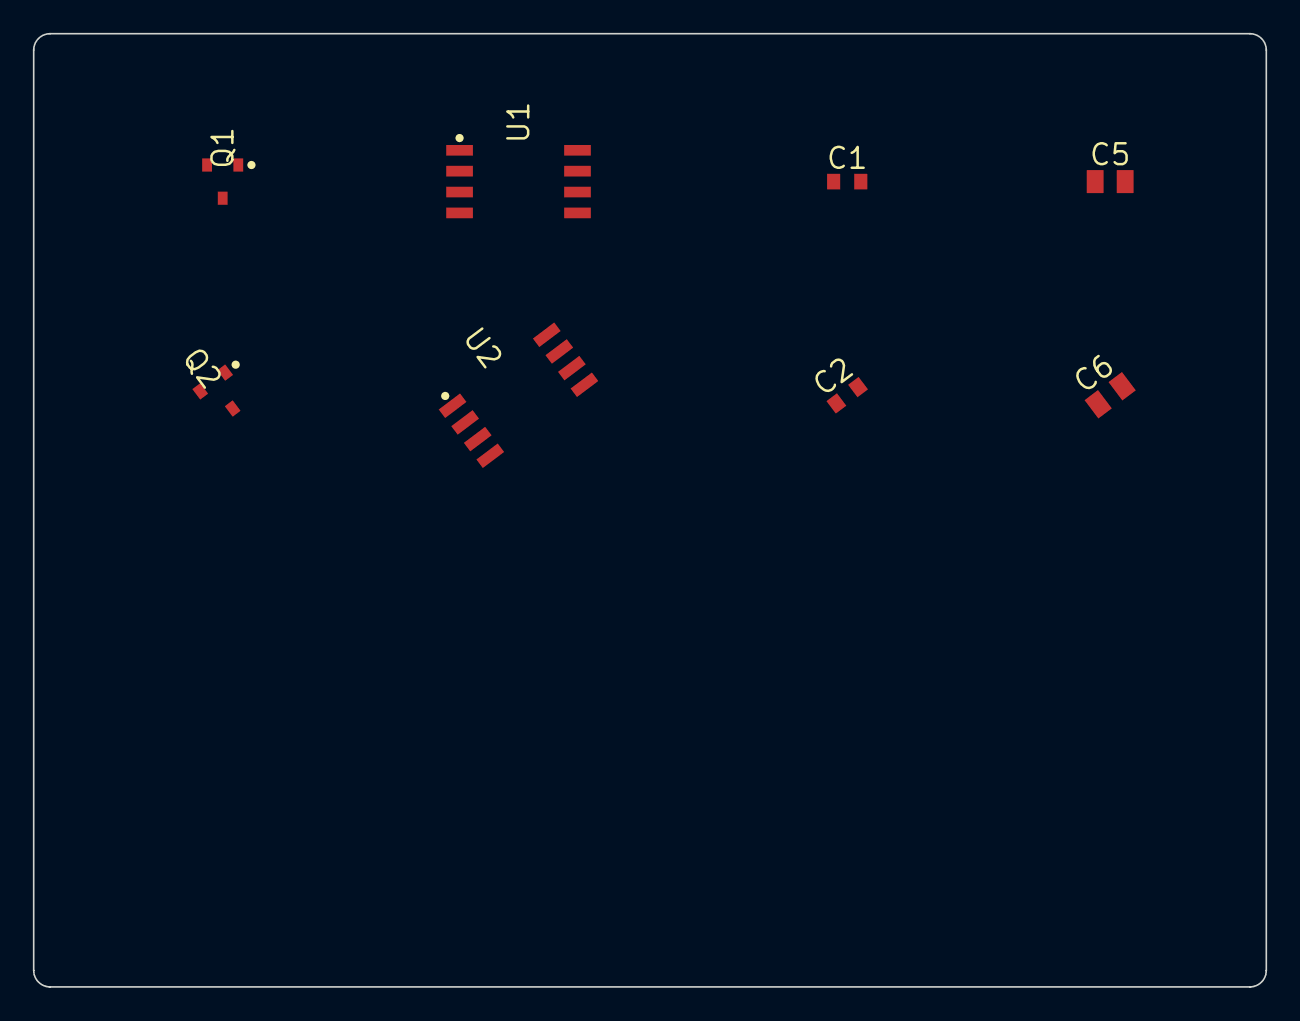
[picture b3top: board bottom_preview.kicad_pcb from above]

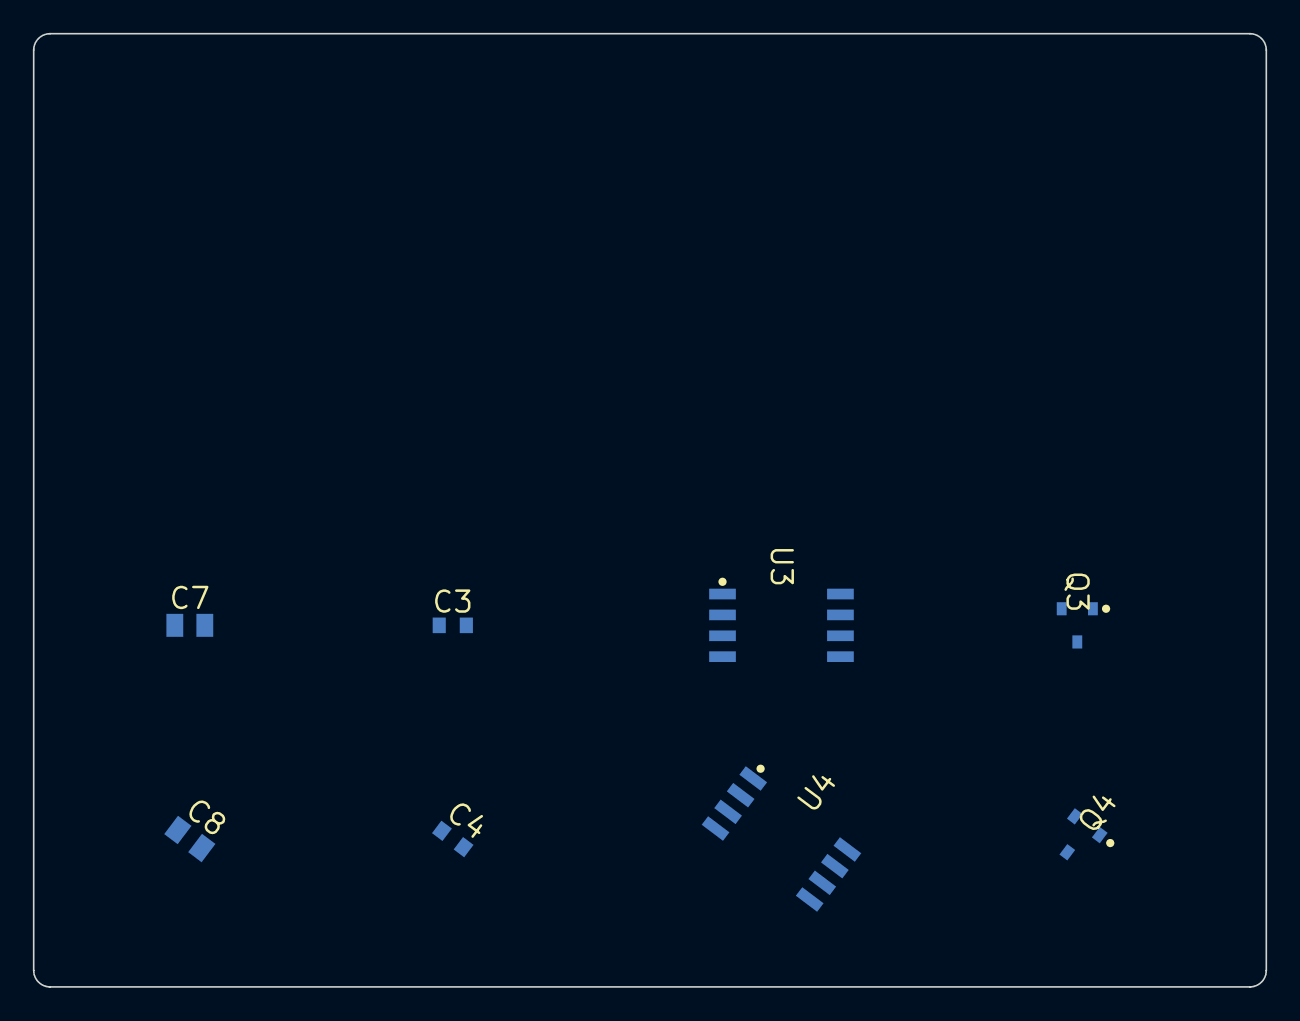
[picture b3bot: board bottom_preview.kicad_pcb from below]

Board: 2 copper layers, 75.0 x 58.0 mm, 16 parts (8 on the bottom side), 2 nets, no tracks yet.

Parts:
C1, C2, C3, C4: 27pF; passive-CHIP_0603
C5, C6, C7, C8: 15pF; passive-CHIP_0805
Q1, Q2, Q3, Q4: NPN_SOT23_BEC; transistor-FP_JSCJ_SOT23
U1, U2, U3, U4: W25Q128JV; soic-SOIC8P127X790X216N

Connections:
GND: C1.2, C2.2, C3.2, C4.2, C5.2, C6.2, C7.2, C8.2, Q1.2, Q2.2, Q3.2, Q4.2, U1.4, U2.4, U3.4, U4.4
V3V3: C1.1, C2.1, C3.1, C4.1, C5.1, C6.1, C7.1, C8.1, Q1.1, Q1.3, Q2.1, Q2.3, Q3.1, Q3.3, Q4.1, Q4.3, U1.8, U2.8, U3.8, U4.8

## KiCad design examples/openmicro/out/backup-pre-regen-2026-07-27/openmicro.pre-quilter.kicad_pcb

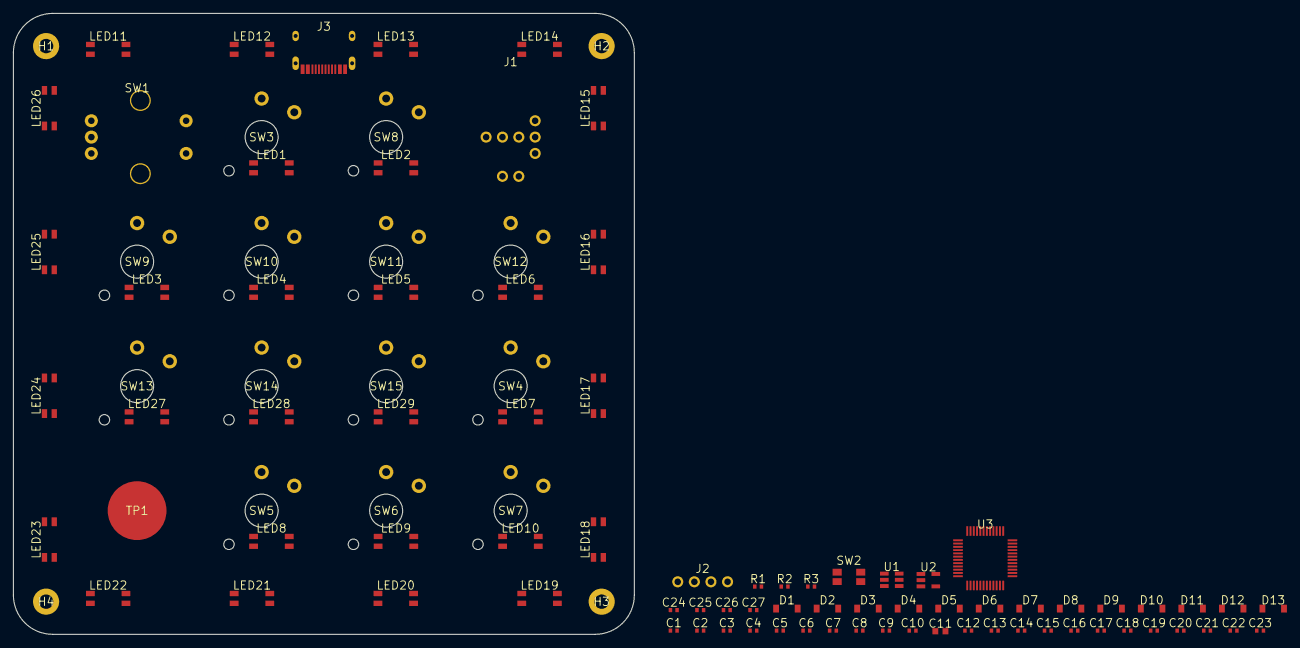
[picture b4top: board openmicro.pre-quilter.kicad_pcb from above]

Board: 2 copper layers, 95.0 x 95.0 mm, 98 parts (0 on the bottom side), 70 nets, no tracks yet.

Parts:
C1, C2, C3, C4, C5, C6, C7, C8, C9, C10, C13, C14, C15, C16, C17, C18, C19, C20, C21, C22, C23, C24, C25, C26, C27: 100nF; std-CHIP_0402
C11: 4.7uF; std-CHIP_0603
C12: 1uF; std-CHIP_0402
D1, D2, D3, D4, D5, D6, D7, D8, D9, D10, D11, D12, D13: Diode_1N4148; openmicro-FP_D_SOD_123
H1, H2, H3, H4: MountingHole; openmicro-FP_MountingHole_M2
J1: ThumbPointer; openmicro-FP_Joystick_RKJXV
J2: SWD_Header; openmicro-FP_Header_1x4
J3: USB_C_Receptacle_2_0; std-FP_USB_C_Receptacle_HRO_TYPE_C_31_M_12
LED1, LED2, LED3, LED4, LED5, LED6, LED7, LED8, LED9, LED10, LED11, LED12, LED13, LED14, LED15, LED16, LED17, LED18, LED19, LED20, LED21, LED22, LED23, LED24, LED25, LED26, LED27, LED28, LED29: SK6812; openmicro-FP_LED_SK6812MINI_E
R1: 10kohm; std-CHIP_0402
R2, R3: 5.1kohm; std-CHIP_0402
SW1: RotaryEC11; openmicro-FP_Encoder_EC11
SW2: ResetSwitch; openmicro-FP_SW_Reset
SW3, SW4, SW5, SW6, SW7, SW8, SW9, SW10, SW11, SW12, SW13, SW14, SW15: KeySwitch; openmicro-FP_SW_Choc_V2
TP1: CapTouchPad; openmicro-FP_TouchPad
U1: USBLC6; openmicro-FP_SOT_23_6
U2: AP2112K_3V3; std-SOT5P95X290X160N
U3: STM32F072CBT6; openmicro-QFP50P900X900X160_48N

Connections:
BOOT0: R1.1, U3.44
CC1: J3.A5, R2.1
CC2: J3.B5, R3.1
COL0: D1.1, D5.1, D9.1, D13.1, U3.25
COL1: D2.1, D6.1, D10.1, U3.26
COL2: D3.1, D7.1, D11.1, U3.27
COL3: D4.1, D8.1, D12.1, U3.28
ENC_A: SW1.1, U3.29
ENC_B: SW1.3, U3.30
ENC_SW: SW1.4, U3.31
GND: C1.2, C2.2, C3.2, C4.2, C5.2, C6.2, C7.2, C8.2, C9.2, C10.2, C11.2, C12.2, C13.2, C14.2, C15.2, C16.2, C17.2, C18.2, C19.2, C20.2, C21.2, C22.2, C23.2, C24.2, C25.2, C26.2, C27.2, H1.1, H2.1, H3.1, H4.1, J1.1, J1.4, J1.8, J2.3, J3.A1, J3.A12, J3.B1, J3.B12, J3.SH1, J3.SH2, J3.SH3, J3.SH4, LED1.3, LED2.3, LED3.3, LED4.3, LED5.3, LED6.3, LED7.3, LED8.3, LED9.3, LED10.3, LED11.3, LED12.3, LED13.3, LED14.3, LED15.3, LED16.3, LED17.3, LED18.3, LED19.3, LED20.3, LED21.3, LED22.3, LED23.3, LED24.3, LED25.3, LED26.3, LED27.3, LED28.3, LED29.3, R1.2, R2.2, R3.2, SW1.2, SW1.5, SW1.6, SW1.7, SW2.3, SW2.4, U1.2, U2.2, U3.8, U3.23, U3.35, U3.47
JOY_SW: J1.7, U3.12
JOY_X: J1.2, U3.10
JOY_Y: J1.5, U3.11
KEY1: D1.2, SW3.2
KEY2: D6.2, SW8.2
KEY3: D7.2, SW9.2
KEY4: D8.2, SW10.2
KEY5: D9.2, SW11.2
KEY6: D10.2, SW12.2
KEY7: D11.2, SW13.2
KEY8: D12.2, SW14.2
KEY9: D13.2, SW15.2
KEY10: D2.2, SW4.2
KEY11: D3.2, SW5.2
KEY12: D4.2, SW6.2
KEY13: D5.2, SW7.2
LED_D0: LED1.4, U3.41
LED_D1: LED1.2, LED2.4
LED_D2: LED2.2, LED3.4
LED_D3: LED3.2, LED4.4
LED_D4: LED4.2, LED5.4
LED_D5: LED5.2, LED6.4
LED_D6: LED6.2, LED27.4
LED_D7: LED27.2, LED28.4
LED_D8: LED28.2, LED29.4
LED_D9: LED7.4, LED29.2
LED_D10: LED7.2, LED8.4
LED_D11: LED8.2, LED9.4
LED_D12: LED9.2, LED10.4
NRST: SW2.1, SW2.2, U3.7
ROW0: SW3.1, SW8.1, SW9.1, SW10.1, U3.18
ROW1: SW11.1, SW12.1, SW13.1, SW14.1, U3.19
ROW2: SW4.1, SW5.1, SW6.1, SW15.1, U3.20
ROW3: SW7.1, U3.21
SWCLK: J2.2, U3.37
SWDIO: J2.1, U3.34
TOUCH: TP1.1, U3.13
UG_D0: LED11.4, U3.40
UG_D1: LED11.2, LED12.4
UG_D2: LED12.2, LED13.4
UG_D3: LED13.2, LED14.4
UG_D4: LED14.2, LED15.4
UG_D5: LED15.2, LED16.4
UG_D6: LED16.2, LED17.4
UG_D7: LED17.2, LED18.4
UG_D8: LED18.2, LED19.4
UG_D9: LED19.2, LED20.4
UG_D10: LED20.2, LED21.4
UG_D11: LED21.2, LED22.4
UG_D12: LED22.2, LED23.4
UG_D13: LED23.2, LED24.4
UG_D14: LED24.2, LED25.4
UG_D15: LED25.2, LED26.4
USBC_DM: J3.A7, J3.B7, U1.3
USBC_DP: J3.A6, J3.B6, U1.1
USB_DM: U1.4, U3.32
USB_DP: U1.6, U3.33
V3V3: C1.1, C2.1, C3.1, C12.1, J1.3, J1.6, J2.4, U2.5, U3.1, U3.9, U3.24, U3.36, U3.48
VBUS: C4.1, C5.1, C6.1, C7.1, C8.1, C9.1, C10.1, C11.1, C13.1, C14.1, C15.1, C16.1, C17.1, C18.1, C19.1, C20.1, C21.1, C22.1, C23.1, C24.1, C25.1, C26.1, C27.1, J3.A4, J3.A9, J3.B4, J3.B9, LED1.1, LED2.1, LED3.1, LED4.1, LED5.1, LED6.1, LED7.1, LED8.1, LED9.1, LED10.1, LED11.1, LED12.1, LED13.1, LED14.1, LED15.1, LED16.1, LED17.1, LED18.1, LED19.1, LED20.1, LED21.1, LED22.1, LED23.1, LED24.1, LED25.1, LED26.1, LED27.1, LED28.1, LED29.1, U1.5, U2.1, U2.3
